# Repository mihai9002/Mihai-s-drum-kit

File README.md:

# Mihai-s-drum-kit:
a macropad drum kit with a digital encoder, so i can switch between presets, and a display to see the current preset
# Components:
- 128x32 OLED Display
- EC11 Rotary encoder for switching between presets
- 7 Switches, the "drums"
# PCB:
- 
- 
# CAD:
- 
- 
- 
# BOM:

- 1x XIAO RP2040
- 7x Cherry MX Switches
- 1x EC11 rotary encoder
- 1x 128x32  0.91" OLED Display
- 7x Blank DSA keycaps
- 4x M3x16mm screws
<<<<<<< HEAD
- 4x M3x5mx4mm heatset inserts
=======
- 4x M3x5mx4mm heatset inserts
>>>>>>> d6a9b59c5bdaede601ab8f5ac71d9ea97c9b7e1e

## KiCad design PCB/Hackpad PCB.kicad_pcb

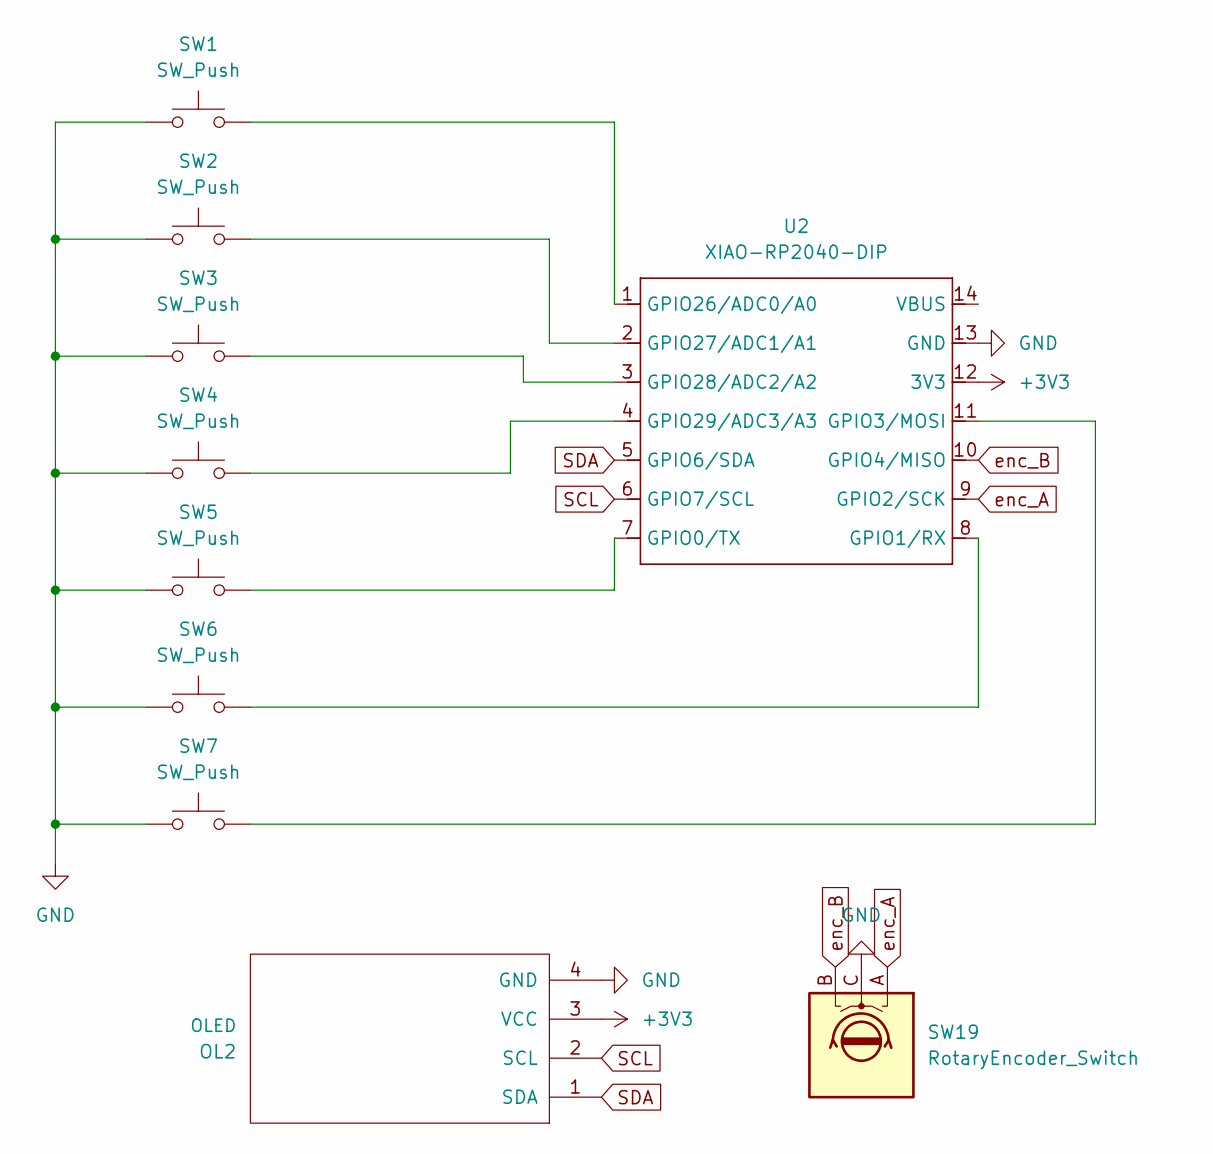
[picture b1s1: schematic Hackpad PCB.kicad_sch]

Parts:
OL2: OLED; SSD1306-0.91-OLED-4pin-128x32
SW1, SW2, SW3, SW4, SW5, SW6, SW7: SW_Push; SW_Cherry_MX_1.00u_PCB
SW19: RotaryEncoder_Switch; RotaryEncoder_Alps_EC11E_Vertical_H20mm_CircularMountingHol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
U2: XIAO-RP2040-DIP

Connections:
+3V3: OL2.3 (VCC), U2.12 (3V3)
GND: OL2.4 (GND), SW1.1, SW2.1, SW3.1, SW4.1, SW5.1, SW6.1, SW7.1, SW19.C, U2.13 (GND)
unnamed: SW5.2, U2.7 (GPIO0/TX)
unnamed: SW6.2, U2.8 (GPIO1/RX)
unnamed: SW7.2, U2.11 (GPIO3/MOSI)
unnamed: SW1.2, U2.1 (GPIO26/ADC0/A0)
unnamed: SW2.2, U2.2 (GPIO27/ADC1/A1)
unnamed: SW3.2, U2.3 (GPIO28/ADC2/A2)
unnamed: SW4.2, U2.4 (GPIO29/ADC3/A3)
SCL: OL2.2 (SCL), U2.6 (GPIO7/SCL)
SDA: OL2.1 (SDA), U2.5 (GPIO6/SDA)
enc_A: SW19.A, U2.9 (GPIO2/SCK)
enc_B: SW19.B, U2.10 (GPIO4/MISO)

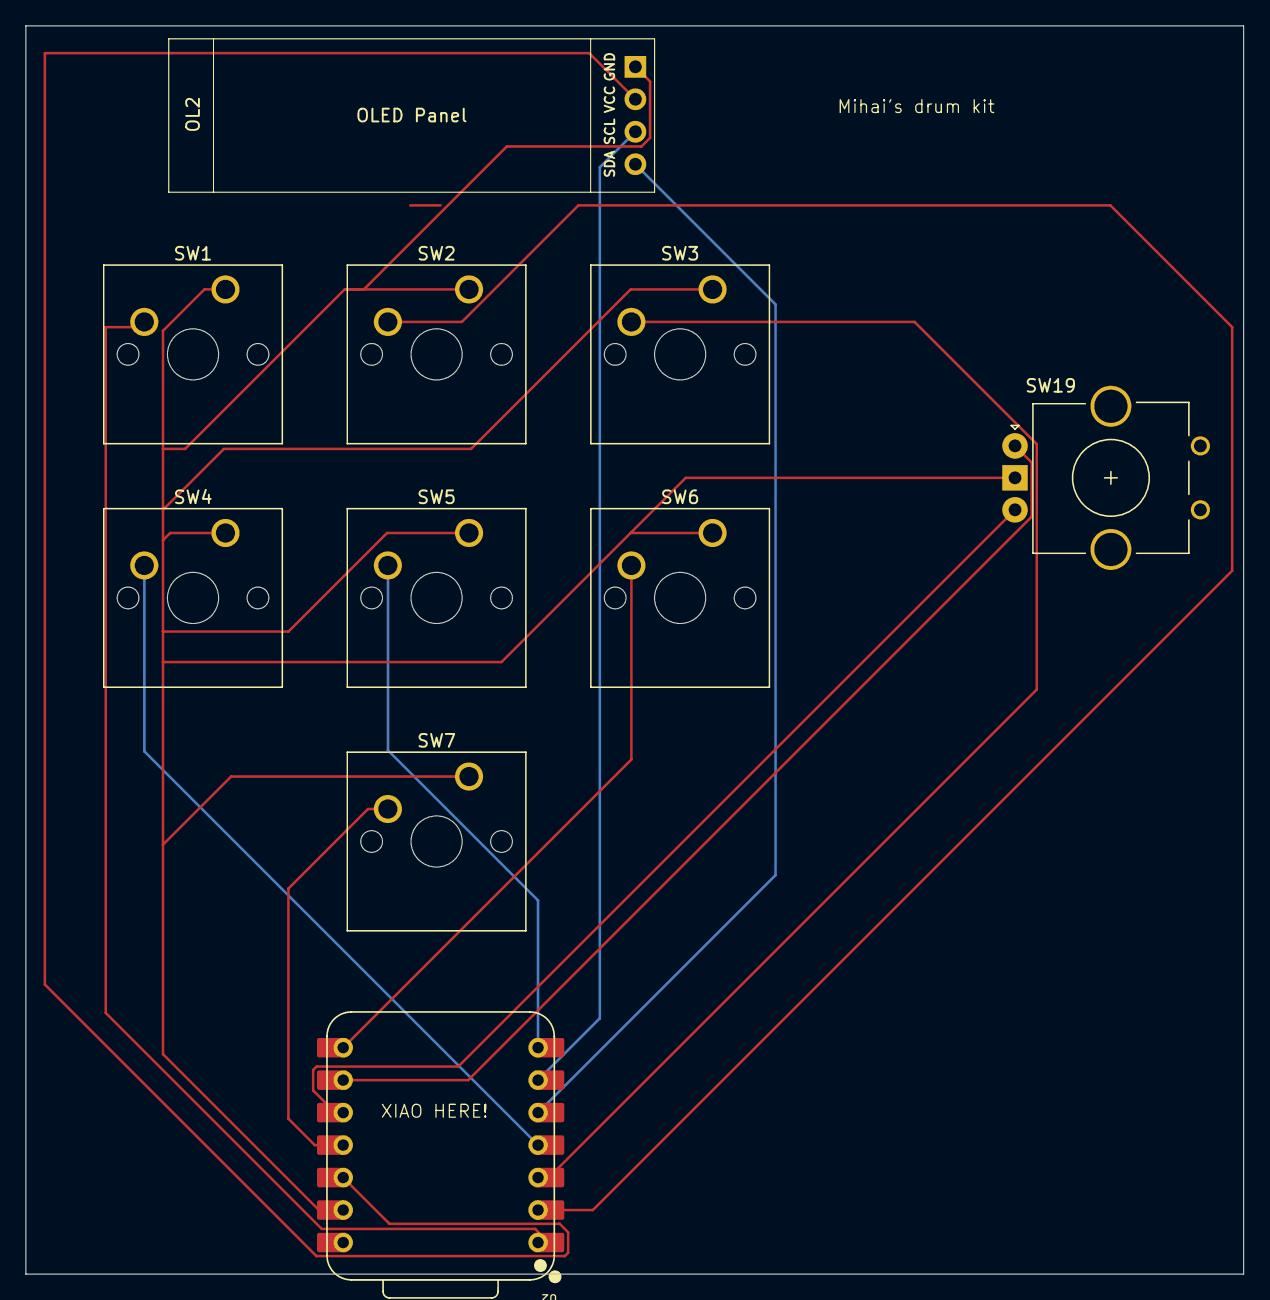
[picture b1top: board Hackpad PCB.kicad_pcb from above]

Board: 2 copper layers, 95.2 x 97.6 mm, 10 parts (0 on the bottom side), 13 nets.

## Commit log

2025-12-24 Add README
2025-12-24 Create Firmware
